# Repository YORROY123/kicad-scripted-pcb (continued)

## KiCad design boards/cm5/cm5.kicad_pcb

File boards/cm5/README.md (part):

# CM5 carrier(進行中)

Raspberry Pi Compute Module 5(含 eMMC)的通用載板,目標是 JLCPCB 能直接 PCBA,CM5 自己插上。

原理圖已完成。PCB 進行中:擺件完成,佈線第一、二階段(兩級降壓的鋪銅與過孔、閘極驅動)完成,第三階段(差分線)全部手佈完成,其餘還沒佈線(交給 freerouting)。3D 預覽在 [`concept/`](concept/README.md)。

## PCB(進行中)

`gen/pcb.py` 讀網表擺出 `cm5.kicad_pcb`;座標與自動擺件在 `gen/placement.py`,3D 預覽也用同一份。
電源級的外層鋪銅、過孔與手佈走線在 `gen/power_stage.py`(見「電源級」「閘極驅動」兩節)。
差分線在 `gen/diff_pairs.py`(見「差分線」)。

- 170 × 120 mm、4 層。固定孔:板子 M3 ×4(H1–H4),CM5 模組 M2.5 ×4(H5–H8)。
- 網路類別(線寬由電流算,見下一節「外層電源走線」):`HV54`(+54V、VIN_RAW;1.4 mm、間距 0.25 mm)、
  `PoE`(POE*;0.5 mm、0.25 mm)、`Switch`(SW、SW3;主路徑是鋪銅)、`Rail5`(+5V;2.7 mm)、`Rail3`(+3V3;1.1 mm)、
  `USB5V`(USB-A / HDMI / USB-C 的 VBUS;0.75 mm)、`Power`(GND 與其他小電源;0.5 mm)。
  54 V 間距取 IPC-2221 表 6-1 的 B4(外層有防焊,51–100 V 0.13 mm)再留餘量;B2(無塗層)的 0.6 mm
  零件本身做不到(RJ45 腳間 0.53、IP804AR 0.25)。
- `cm5.kicad_dru`:同一顆零件的焊盤之間最小 0.1 mm(FSUSB42 MSOP-10 焊盤間只有 0.15 mm),
  走線與過孔仍照網路類別。拿掉這個檔,DRC 會報 FSUSB42 的 8 個間距錯誤。
- 自檢(`lib/pcbgen.py`):焊盤逐腳對網表、courtyard 真實多邊形不重疊、不出板(板邊接頭只查焊盤)。
  `build.ps1` 與 CI 再跑 DRC + 原理圖一致性,除了未連接以外不能有錯誤。
- SW51(FLASH/RUN 滑動開關):撥桿在封裝局部 +y,所以 0°;固定腳到 y=1.83,銅到板邊要 ≥0.5 mm,
  本體退到板邊內 0.75 mm,撥桿伸出約 0.8 mm。外殼開孔時要確認撥得到。

### 差分阻抗(`sim/diff_impedance.py`,結果 `sim/diff_impedance.txt`)

目標照 CM5 規格書 §2.2–2.5:PCIe、USB 3.0、USB 2.0 都是 **90 Ω**,HDMI 與乙太網路 **100 Ω**
(先前這裡寫 PCIe 85 Ω 是錯的)。疊構 JLC04161H-3313(jlcpcb.com/impedance):L1 銅 0.035 mm、
3313 預浸料 0.0994 mm、εr 4.1,差分線走 L1、參考 L2 整片地(L4 對 L3 疊構相同,但 L3 是電源平面,只用來短暫下穿)。`lib/field2d.py` 外推到格距 → 0:

| 用途 | 目標 | 線寬 | 間距 | 算出 |
|---|---|---|---|---|
| PCIe / USB3 / USB2 | 90 Ω | 0.165 mm | 0.15 mm | 90.5 Ω |
| 同上(較緊) | 90 Ω | 0.155 mm | 0.13 mm | 91.0 Ω |
| HDMI / Ethernet | 100 Ω | 0.145 mm | 0.20 mm | 100.2 Ω |
| 同上(較緊) | 100 Ω | 0.130 mm | 0.15 mm | 101.0 Ω |

- 同層鋪銅離差分線 ≥ 0.25 mm 時,阻抗只低 0.4%;0.15 mm 會低 1.5%。
- 防焊漆沒建模(實際再低約 1–3 Ω),所以結果故意落在目標上方。下單前要用 JLC 自己的計算器
  (有建模防焊與梯形線)對一次,並選阻抗控制。
- 換層:L1 ↔ L4 的參考面從 L2(地)換成 L3(電源),旁邊放地過孔接不到 L3,沒有用;要的是 GND–電源的
  縫合電容(見「差分線」待辦)。L4 段不能跨 L3 的 +5V / +3V3 分界。

### 外層電源走線(`gen/pcb.py` 的 `CURRENTS`)

IPC-2221 §6.2 外層公式,外層 1 oz(0.035 mm)、溫升 10 °C。電流取「保護動作前能一直流的電流」:
限流開關用限流**上限**,不是額定。網路類別的線寬比算出的窄,`gen/pcb.py` 就刪掉板檔、回傳失敗。

| 網 | 電流 | 依據 | 需要 | 類別線寬 |
|---|---|---|---|---|
| VIN_RAW、+54V | 3.0 A | 120 W ÷ UVLO 40 V | 1.37 mm | 1.4 mm |
| POE0/1_P、_N | 0.92 A | IP804AR 限流上限(保險絲 1.5 A 只在故障時斷) | 0.27 mm | 0.5 mm |

+5V(→ U62/U63/U70、CM5)與 +3V3(→ M.2)的外層大電流路徑改由「外層供電支線」的鋪銅檢查,
類別線寬降回焊盤放得下的寬度(+5V 0.4、+3V3 0.25),見下一節。
| USBA0/1_VBUS | 1.9 A | AP2171W 限流上限 | 0.73 mm | 0.75 mm |
| HDMI_5V | 1.05 A | TPS2051C 限流上限 | 0.32 mm | 0.75 mm |

- 開關節點與降壓器輸出到內層平面的過孔見下一節「電源級」。
- ⚠ +5V 預算:LM5146 設計 12 A。額定負載 CM5 5 A + 40-pin 1 A + 風扇 0.5 A + USB-A 2 × 1 A + HDMI 0.5 A
  + TPS568230 輸入約 3.0 A(3.3 V × 4 A ÷ 90% ÷ 4.87 V)≈ 12.0 A,剛好到頂。所有限流開關都頂到上限時
  約 14.4 A,會先碰到 LM5146 的限流。要不要降 USB-A 的限流檔或改 12 A 以上的降壓器,佈線前決定。
- `gen/board.py` 的 TPS2051C 註解原本寫限流 0.5–0.9 A,規格書 §6.7(−40–125 °C)是 0.65–1.05 A,已改。

### 外層供電支線(`gen/feeds.py`)與平面扇出(`lib/fanout.py`)

網路類別的線寬整條網共用。+5V 原本 2.7 mm、+3V3 1.1 mm 是照最大的支路算的,結果 LAN7800 / USB2514B
0.25 mm 寬、0.5 mm 腳距的 QFN 腳也要接 1.1 mm 的線,freerouting 扇不出去。現在大電流路徑用固定鋪銅畫死:

| 支線 | 電流 | 做法 | 過孔(每個 0.71 A) |
|---|---|---|---|
| In2 +5V → U62、U63、U70 | 4.85 A | 開關擺在 In2 的 +3V3 區:CM5 模組底邊過孔陣列 → B.Cu 主幹 x 89.5–93.6(避開 USBA0 下穿)→ y 91.3–95.6 橫向 → 每顆 5 腳旁一小塊 F.Cu | 12 / 3 / 3 / 2 |
| In2 +5V → CM5 J1 77–87 | 5 A | 腳下方 F.Cu + 5×2 過孔 | 10 |
| In2 +3V3 → M.2 3V3 腳 | 2.5 A | 右排三組腳外側(卡底下)各一塊 F.Cu | 2 / 3 / 2 |

自檢:載流截面(B.Cu 主幹 3.70 mm ≥ 2.65)、過孔數、F.Cu 小鋪銅的過孔也要落在 B.Cu 主幹上、
每支目標腳最後都接到同網的 In2 平面。突變:U62 過孔 3 → 2、M.2 2/4 腳的鋪銅右移離開焊盤,都會失敗。

平面網路(GND → In1、+3V3 / +5V → In2)的 SMD 焊盤由 `lib/fanout.py` 先打好過孔 + 短線(鎖定):
過孔要落在該網平面的銅上、與異網銅保持兩邊類別較大的間距、孔距 0.25、不進其他零件 courtyard;
短線不比焊盤窄邊寬(CM5 連接器 0.2 mm 焊盤用 0.25 的線離隔壁腳只剩 0.175)。QFN 散熱焊盤
(U40、U41、U50、U61)焊盤內 3×3 過孔。目前 302 個過孔,找不到位置 9 個(C210 / C213 / C230 那裡
In2 是 +3V3 區,沒有 +5V 平面可接,由佈線接到供電支線)。DRC 0。

### 內層電源平面(`gen/pcb.py` 的 `PLANES` / `CORRIDORS`)

- L2(In1.Cu)整片 GND,當 L1 差分線的參考面。
- L3(In2.Cu)分兩塊、中間留 0.5 mm:**+5V** 在右上(x ≥ 60、y ≤ 72),L10 降壓輸出 → CM5、40-pin、風扇;
  **+3V3** 是 L 形(下緣 y ≥ 72 + 左緣 x ≤ 60),L20 降壓輸出 → Hub、LAN7800 ×2 → 往上到 M.2。
- 自檢:每條載流走廊要整塊落在該網的平面裡,而且寬度 ≥ IPC-2221 §6.2 內層公式算出的寬度
  (JLC 內層銅 0.0152 mm、溫升 10 °C;對平面很保守)。不過就刪掉板檔、回傳失敗。

| 網 | 電流 | 走廊寬 | IPC-2221 需要 |
|---|---|---|---|
| +5V(L10 → CM5、40-pin、風扇) | 6.5 A | 71.5 mm | 23.8 mm |
| +3V3(L20 → Hub、LAN7800) | 4.0 A | 47.5 mm | 12.2 mm |
| +3V3(左緣 → M.2) | 2.5 A | 59.5 mm | 6.4 mm |

電流:CM5 5 V 最多 5 A(規格書 §1);M.2 3.3 V 2.5 A(M.2 規範上限);LAN7800 ×2 0.592 A;
40-pin 1 A、風扇 0.5 A、其他 3.3 V 0.3 A 是估計。注意 IPC-2221 這個寬度是 0.5 oz 內層的值:
若整顆降壓器 12 A 都走平面,需要約 55 mm,現在的佈局給得起,但 USB/HDMI 的 5 V 不走平面。
突變:+5V 平面下緣縮到 y = 50 → 走廊落在平面外;+5V 電流改 30 A → 寬度不足,兩者都會失敗。
平面只刪小於 3 mm² 的孤島(`PLANE_MIN_ISLAND_MM2`):40-pin 排針腳之間約 2.2 mm² 的碎銅、過孔陣列之間
< 0.5 mm² 的碎銅都沒接任何東西,以前留著,DRC 報 22 個 isolated_copper 警告;現在 0 個。
還沒接到焊盤的整塊平面不刪。

### 電源級(佈線第一階段;`gen/power_stage.py`)

功率件改成手擺(`gen/placement.py` 的 `PLACE`),照 LM5146 規格書 SNVSBV0A §11.1 與 TPS568230 SLVSEY5C §10.1
(兩份都在 TI 官網);小件仍自動擺,但避開鋪銅與過孔(`power_stage.keepouts()`)。

- **LM5146 → +5V**:Q10 轉 180、Q11 不轉,上下疊。開關節點(Q10 源極、Q11 汲極 → L10)在右側一直線;
  熱迴路(輸入電容 → Q10 汲極 … Q11 源極 → 電容)在左側,C11/C13/C16 的 + 端貼 Q10 汲極、− 端貼 Q11 源極,
  地過孔靠 Q11 源極(§11.1.5)。U10 轉 270,閘極驅動腳朝下正對 Q10;VCC、自舉電容(C20、C21)在 U10 與 Q10 之間。
  54 V 輸入 J20 移到右上,F1 → C10 → 一條 2.1 mm 的 +54V 鋪銅帶往下接輸入電容。
- **TPS568230 → +3V3**:U20 轉 180,VIN 朝右接 C45、SW(19/20 腳)朝下接 L20。整級跨在 In2 分界上:
  輸入取 +5V 平面(5 個過孔),L20 的 2 腳在 +3V3 平面上(8 個過孔)。
- 13 塊 F.Cu 鋪銅都有名字、優先序 1(蓋過之後的整面 GND);80 個過孔鎖定。`lib/route.py` 重新匯入佈線時
  留下它們(`lib/route_test.py`),匯出的 DSN 裡鋪銅是 `plane`、過孔是 `(type fix)`,freerouting 不會動。
- 自檢(`gen/pcb.py` 的 `add_power_stage`,不過就刪掉板檔):每塊鋪銅填得出來、每個過孔在自己網的銅上、
  載流截面整塊有銅、過孔數夠:

| 截面 / 過孔 | 電流 | 寬 | IPC-2221 外層 | 判斷 |
|---|---|---|---|---|
| +54V 帶子(F1 / C10 → 輸入電容) | 3.0 A | 1.7 mm | 1.37 mm | 寬度夠 |
| SW:Q11 汲極 → L10(長 2.35 mm) | 12 A | 4.5 mm | 9.25 mm | 短頸,I²R 37 mW |
| SW3:U20 腳 → L20(長 0.9 mm) | 8 A | 0.85 mm | 5.29 mm | 短頸,I²R 33 mW;受限於 IC 腳寬 |
| +5V:L10 2 腳 → 第一排過孔(長 0.45 mm) | 12 A | 6.3 mm | 9.25 mm | 短頸,I²R 5 mW |
| +3V3:L20 2 腳 → 過孔與輸出電容(長 3.6 mm) | 4.0 A | 2.9 mm | 2.03 mm | 寬度夠 |
| 過孔 L10 → In2 +5V | 12 A | 27 個 | 至少 17 | |
| 過孔 In2 +5V → U20 | 3.0 A | 5 個 | 至少 5 | |
| 過孔 L20 → In2 +3V3 | 4.0 A | 8 個 | 至少 6 | |

  IPC-2221 的寬度是長走線的溫升;開關節點 TI 要求面積越小越好(§11.1.4,它是 EMI 來源),所以 ≤ 3 mm 的
  短頸改算 I²R(銅 1.72e-5 Ω·mm),上限 0.1 W(MOSFET 本身約 1 W 量級)。截面取兩端焊盤之間整段窄處,
  長度照實(只切一薄片的話,任何電流都會被當成短頸放過)。
  突變:拿掉 12 個 +5V 過孔、SW 鋪銅縮窄、過孔移出銅、+3V3 電流改 9 A,四種都會失敗。
- 過孔數改了:以前寫 L10 → +5V 平面 6.5 A、10 個,只算了 CM5、40-pin、風扇;USB-A / HDMI 開關和 U20 的輸入
  也從 +5V 平面取電,LM5146 設計的 12 A 全部要經過這些過孔 → 至少 17 個。
- 還沒做:U10、U20 散熱焊盤下的地過孔(TI §11.1.4):過孔打在焊盤裡要選 JLC 的樹脂塞孔,下單前決定。

### 閘極驅動(佈線第二階段;`gen/power_stage.py` 的 `TRACKS`)

手佈、鎖定的 28 段走線與 4 個過孔(DSN 裡都是 `(type fix)`)。U10 底排腳距 0.5 mm,由左到右
12 GND、13 LO、14 VCC、15 GND、16 NC、17 BST、18 HO、19 SW;腳間出線只能 0.24–0.25 mm,離開腳位才加寬。

- **C21(自舉)不跨 HO**:第一階段以為一定要過孔。改成直放在 16 腳(NC)下:上端直連 17 腳 BST,
  下端一條 0.4 mm 線從 Q10 汲極與閘極焊盤之間直下 SW 鋪銅。HO(18 腳)0.65 mm 直下 Q10 閘極,
  19 腳 SW 在它右側並行回 Q10 源極,即 TI §11.1.2 的「HO 與 SW 成對走」。
- **C20(VCC)轉 180°**:GND 端在 12 腳下、VCC 端在 14 腳下,都是直線;兩焊盤之間 0.65 mm 剛好讓 LO 出去。
- **LO**:過孔換到 B.Cu,0.65 mm 直線到 Q11 閘極,約 12 mm,是唯一換層的閘極線。Q11 的源極要朝左接熱迴路,
  閘極腳就只能在左下角。B.Cu 下面的參考面是 In2 +5V(交流上等同地)。
- **U20 6 腳**(SW3 的另一支,上方是 C47、右邊是 +5V 輸入):C47 往上挪 0.6 mm,6 腳打過孔走 B.Cu 回 SW3 鋪銅。
  B.Cu 走 +5V 腳下方,不經 EP 正下方,留給散熱過孔。
- 也手佈了 C47 → 8 腳 GND 與 +5V 鋪銅、BST3(1 腳 → C49,穿過 SW3 鋪銅的缺口)。VCC3(C48)交給 freerouting。
- 自檢:HO、LO、BST、VCC、SW3、BST3 每條網的焊盤都要接通(`GetConnectedItems`)。
  突變:HO 截短到閘極前、刪掉 6 腳那段,都會失敗。DRC 0 錯誤;未接數(pcbnew 實算)695 → 684。
  `kicad-cli` 報告的「499 unconnected」是它的上限,不是實際數字。

### 差分線(佈線第三階段;`gen/diff_pairs.py`)

每對寫一條中心線,程式切 45° 角、往兩側偏移出 P、N(線寬 / 間距照「差分阻抗」),兩端自動接到 P、N 網的
焊盤;換層處放一對過孔(中心距 1 mm)。走線與過孔都鎖定。對內間距 0.15 mm 比網路類別的 0.2 mm 小,
`cm5.kicad_dru` 每對加一條規則(下限 0.14,留給座標捨入)。

| 對 | 長 | 換層 | 說明 |
|---|---|---|---|
| PCIe REFCLK | 127 mm | 0 | J2 頂排往北 → 向西 → 從 M.2 插座南端繞到腳後 |
| PCIe TX | 128 mm | 0 | 同上 |
| PCIe RX | 122 mm | 1 | 在 x ≈ 45 從 TX 底下穿過(B.Cu 約 4 mm,L3 為 +3V3) |
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
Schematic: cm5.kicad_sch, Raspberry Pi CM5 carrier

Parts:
BT50: CR2032; BatteryHolder_Keystone_3034_1x20mm
C10: 100uF; CP_Radial_D12.5mm_P5.00mm
C11, C12, C13, C14, C15, C16: 4.7uF; C_1210_3225Metric
C17: 100nF; C_0603_1608Metric
C18: 47nF; C_0402_1005Metric
C19: 15pF; C_0402_1005Metric
C20: 2.2uF; C_0603_1608Metric
C21, C47, C49, C51, C60, C70, C71, C72, C73, C74, C75, C76, C77, C88, C101, C102, C103, C104, C106, C107, C108, C109, C111, C112, C113, C114, C115, C120, C121, C131, C132, C133, C134, C136, C137, C138, C139, C141, C142, C143, C144, C145, C150, C151, C200, C202, C203, C204, C205, C206, C207, C212, C215, C222, C230, C231, C240, C241, C242, C243, C244, C245, C246, C247, C248, C249, C250, C251, C252, C253: 100nF; C_0402_1005Metric
C22: 6.8nF; C_0402_1005Metric
C23: 150pF; C_0402_1005Metric
C24: 820pF; C_0402_1005Metric
C30, C31, C32, C33, C34, C40, C41, C42, C43, C45, C46, C50, C220, C221: 47uF; C_1210_3225Metric
C44: 100pF; C_0402_1005Metric
C48, C105, C117, C135, C147, C210, C213: 1uF; C_0402_1005Metric
C82: 1uF; C_1206_3216Metric
C83: 47uF; CP_Elec_10x10
C84, C85, C86, C87, C201: 4.7uF; C_0603_1608Metric
C90, C91: 1nF 2kV; C_1206_3216Metric
C92, C93: 100nF; C_0805_2012Metric
C100, C110, C130, C140: 10uF; C_0805_2012Metric
C118, C119, C148, C149: 27pF; C_0402_1005Metric
C208, C209: 22pF; C_0402_1005Metric
C211, C214: 100uF; CP_Elec_6.3x7.7
D20, D60, D61: SM6T68A; D_SMB
D40, D42, D51: GREEN; LED_0805_2012Metric
D41, D43: YELLOW; LED_0805_2012Metric
D50: RED; LED_0805_2012Metric
D70, D71, D72: USBLC6-2SC6; SOT-23-6
F1: 4A 63V; Fuse_1206_3216Metric
F40, F41: 1.5A; Fuse_1206_3216Metric
J1: CM5 pins 1-100; Amphenol_10164227-1001A1RLF_2x50_P0.4mm
J2: CM5 pins 101-200; Amphenol_10164227-1001A1RLF_2x50_P0.4mm
J20: 54V IN; TerminalBlock_Phoenix_MKDS-1,5-2-5.08_1x02_P5.08mm_Horizont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
J30: HR911130A; RJ45_Hanrun_HR911130A_Horizontal
J40: POE0; RJ45_Amphenol_RJHSE5380
J41: POE1; RJ45_Amphenol_RJHSE5380
J50: USB-C FLASH; USB_C_Receptacle_HRO_TYPE-C-31-M-12
J51: USB-A 1; USB_A_Molex_48037-2200_Horizontal
J52: USB-A 2; USB_A_Molex_48037-2200_Horizontal
J60: M.2 M-key; M.2_Socket_M_TE_1-2199230-6
J70: HDMI; HDMI_A_Molex_208658-1001_Horizontal
J80: GPIO 40-pin; PinHeader_2x20_P2.54mm_Vertical
J81: FAN; JST_SH_SM04B-SRSS-TB_1x04-1MP_P1.00mm_Horizontal
L10: 3.3uH SPM10065VT; L_Bourns_SRP1050WA
L20: 1.5uH IHLP4040; L_Vishay_IHLP-4040
L40, L41: 3.3uH; L_1008_2520Metric
Q10: BSC160N10NS3G; TDSON-8-1
Q11: BSC070N10NS5; TDSON-8-1
R10: 402k; R_0805_2012Metric
R11: 12.4k; R_0402_1005Metric
R12: 33.2k; R_0402_1005Metric
R13: 412; R_0805_2012Metric
R14: 23.2k; R_0402_1005Metric
R15: 4.42k; R_0402_1005Metric
R16: 7.5k; R_0402_1005Metric
R17: 150; R_0402_1005Metric
R18, R74, R75, R76, R77, R78, R102, R132, R205, R206, R207, R208, R209, R230: 10k; R_0402_1005Metric
R21: 91k; R_0402_1005Metric
R22: 20k; R_0402_1005Metric
R23: 330k; R_0402_1005Metric
R24, R200, R201: 5.1k; R_0402_1005Metric
R25, R202, R203, R204: 100k; R_0402_1005Metric
R50, R51: 1k; R_0402_1005Metric
R60, R61, R104, R105, R134, R135: 470; R_0402_1005Metric
R80, R81, R82, R83: 75; R_0603_1608Metric
R100, R130: 2k; R_0402_1005Metric
R101, R131, R210: 12k; R_0402_1005Metric
R211: 1M; R_0402_1005Metric
SW50: POWER; SW_Push_1P1T_NO_CK_KMR2
SW51: FLASH/RUN; SW_SPDT_PCM12
T40, T41: G2423S; Transformer_CNDtek_G2423S
U10: LM5146RGYR; Texas_RGY_R-PVQFN-N20_EP2.05x3.05mm
U20: TPS568230RJER; Texas_RJE0020A_VQFN-20-1EP_3x3mm_P0.45mm_EP0.675x0.76mm
U30, U31: TPD4EUSB30; USON-10_2.5x1.0mm_P0.5mm
U40, U41: LAN7800/Y9X; QFN-48-1EP_7x7mm_P0.5mm_EP5.3x5.3mm
U50: IP804AR; QFN-48-1EP_7x7mm_P0.5mm_EP5.3x5.3mm
U60: FSUSB42MUX; MSOP-10_3x3mm_P0.5mm
U61: USB2514B; QFN-36-1EP_6x6mm_P0.5mm_EP3.7x3.7mm
U62, U63: AP2171W; SOT-23-5
U70: TPS2051CDBV; SOT-23-5
Y40, Y41: 25MHz; Crystal_SMD_3225-4Pin_3.2x2.5mm
Y60: 24MHz; Crystal_SMD_2520-4Pin_2.5x2.0mm

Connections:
+3V3: C40.1, C41.1, C42.1, C43.1, C44.1, C100.1, C101.1, C102.1, C103.1, C104.1, C130.1, C131.1, C132.1, C133.1, C134.1, C201.1, C202.1, C203.1, C204.1, C205.1, C220.1, C221.1, C222.1, C240.1, C246.1, C247.1, C248.1, C249.1, C250.1, C251.1, C252.1, C253.1, D40.2 (A), D41.2 (A), D42.2 (A), D43.2 (A), J60.2 (3.3V), J60.4 (3.3V), J60.12 (3.3V), J60.14 (3.3V), J60.16 (3.3V), J60.18 (3.3V), J60.70 (3.3V), J60.72 (3.3V), J60.74 (3.3V), L20.2, R21.1, R25.1, R205.1, R206.1, R207.1, R208.1, R209.1, U40.14 (VDD_SW_IN), U40.20 (VDDVARIO), U40.23 (VBUS_DET), U40.36 (VDDVARIO), U40.38 (VDD33A), U40.39 (VDDVARIO), U40.46 (VDD33_REG_IN), U41.14 (VDD_SW_IN), U41.20 (VDDVARIO), U41.23 (VBUS_DET), U41.36 (VDDVARIO), U41.38 (VDD33A), U41.39 (VDDVARIO), U41.46 (VDD33_REG_IN), U61.5 (VDDA33), U61.10 (VDDA33), U61.15 (VDD33), U61.23 (VDD33), U61.27 (VBUS_DET), U61.29 (VDDA33), U61.36 (VDDA33)
+5V: C30.1, C31.1, C32.1, C33.1, C34.1, C45.1, C46.1, C47.1, C50.1, C51.1, C210.1, C213.1, C230.1, C241.1, C242.1, C243.1, C244.1, C245.1, J1.77 (5V), J1.79 (5V), J1.81 (5V), J1.83 (5V), J1.85 (5V), J1.87 (5V), J80.2, J80.4, J81.1, L10.2, R14.1, R17.1, U20.2 (VIN), U20.3 (VIN), U20.4 (VIN), U20.5 (VIN), U62.5 (IN), U63.5 (IN), U70.5 (IN)
+54V: C10.1, C11.1, C12.1, C13.1, C14.1, C15.1, C16.1, C17.1, C82.1, C83.1, D20.1 (A1), F1.2, F40.1, F41.1, Q10.5 (D), R10.1, U10.20 (VIN), U50.17 (V54)
BST: C21.1, U10.17 (BST)
BST3: C49.1, U20.1 (BST)
CM5U0_RX_N: C120.2, J2.28 (USB3-0-RX_N)
CM5U0_RX_P: C121.2, J2.30 (USB3-0-RX_P)
CM5U1_RX_N: C151.2, J2.57 (USB3-1-RX_N)
CM5U1_RX_P: C150.2, J2.59 (USB3-1-RX_P)
CM5_1V8: J1.88 (CM5_1.8V), J1.90 (CM5_1.8V)
CM5_3V3: C200.1, D50.2 (A), D51.2 (A), J1.78 (GPIO_VREF), J1.84 (CM5_3.3V), J1.86 (CM5_3.3V), J30.11 (LEDG_A), J30.14 (LEDY_A), J80.1, J80.17, R18.1, R230.1, U60.1 (VCC), U70.4 (EN)
CM5_USB_N: J2.3 (USB_N), U60.4 (D-)
CM5_USB_P: J2.5 (USB_P), U60.3 (D+)
COMP: C23.1, R16.1, U10.4 (COMP)
COMP_RC: C22.1, R16.2
EN_UVLO: R10.2, R11.1, U10.1 (EN/UVLO)
ETH0_N: J1.10 (Ethernet_Pair0_N), J30.3 (MDI0-), U30.4 (D2+), U30.7 (NC)
ETH0_P: J1.12 (Ethernet_Pair0_P), J30.2 (MDI0+), U30.5 (D2-), U30.6 (NC)
ETH1_N: J1.6 (Ethernet_Pair1_N), J30.4 (MDI1+), U30.2 (D1-), U30.9 (NC)
ETH1_P: J1.4 (Ethernet_Pair1_P), J30.7 (MDI1-), U30.1 (D1+), U30.10 (NC)
ETH2_N: J1.9 (Ethernet_Pair2_N), J30.5 (MDI2+), U31.4 (D2+), U31.7 (NC)
ETH2_P: J1.11 (Ethernet_Pair2_P), J30.6 (MDI2-), U31.5 (D2-), U31.6 (NC)
ETH3_N: J1.5 (Ethernet_Pair3_N), J30.9 (MDI3-), U31.2 (D1-), U31.9 (NC)
ETH3_P: J1.3 (Ethernet_Pair3_P), J30.8 (MDI3+), U31.1 (D1+), U31.10 (NC)
ETH_CT: C60.1, J30.1 (CT)
ETH_LEDG_K: J30.12 (LEDG_K), R60.1
ETH_LEDY_K: J30.13 (LEDY_K), R61.1
ETH_nACT: J1.15 (Ethernet_nLED3), R60.2
ETH_nSPD: J1.17 (Ethernet_nLED2), R61.2
FAN_PWM: J1.19 (Fan_PWM), J81.2, R230.2
FAN_TACHO: J1.16 (Fan_Tacho), J81.4
FB: C22.2, C23.2, C24.2, R14.2, R15.1, U10.5 (FB)
FB3: C44.2, R21.2, R22.1, U20.14 (FB)
FB_FF: C24.1, R17.2
GND: BT50.2 (-), C10.2, C11.2, C12.2, C13.2, C14.2, C15.2, C16.2, C17.2, C18.2, C19.2, C20.2, C30.2, C31.2, C32.2, C33.2, C34.2, C40.2, C41.2, C42.2, C43.2, C45.2, C46.2, C47.2, C48.2, C50.2, C51.2, C60.2, C70.2, C71.2, C72.2, C73.2, C74.2, C75.2, C76.2, C77.2, C82.2, C83.2, C84.2, C85.2, C86.2, C87.2, C88.2, C90.2, C91.2, C100.2, C101.2, C102.2, C103.2, C104.2, C105.2, C106.2, C107.2, C108.2, C109.2, C110.2, C111.2, C112.2, C113.2, C114.2, C115.2, C117.2, C118.2, C119.2, C130.2, C131.2, C132.2, C133.2, C134.2, C135.2, C136.2, C137.2, C138.2, C139.2, C140.2, C141.2, C142.2, C143.2, C144.2, C145.2, C147.2, C148.2, C149.2, C200.2, C201.2, C202.2, C203.2, C204.2, C205.2, C206.2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
GPIO2: J1.58 (GPIO2), J80.3
GPIO3: J1.56 (GPIO3), J80.5
GPIO4: J1.54 (GPIO4), J80.7
GPIO5: J1.34 (GPIO5), J80.29
GPIO6: J1.30 (GPIO6), J80.31
GPIO7: J1.37 (GPIO7), J80.26
GPIO8: J1.39 (GPIO8), J80.24
GPIO9: J1.40 (GPIO9), J80.21
GPIO10: J1.44 (GPIO10), J80.19
GPIO11: J1.38 (GPIO11), J80.23
GPIO12: J1.31 (GPIO12), J80.32
GPIO13: J1.28 (GPIO13), J80.33
GPIO14: J1.55 (GPIO14), J80.8
GPIO15: J1.51 (GPIO15), J80.10
GPIO16: J1.29 (GPIO16), J80.36
GPIO17: J1.50 (GPIO17), J80.11
GPIO18: J1.49 (GPIO18), J80.12
GPIO19: J1.26 (GPIO19), J80.35
GPIO20: J1.27 (GPIO20), J80.38
GPIO21: J1.25 (GPIO21), J80.40
GPIO22: J1.46 (GPIO22), J80.15
GPIO23: J1.47 (GPIO23), J80.16
GPIO24: J1.45 (GPIO24), J80.18
GPIO25: J1.41 (GPIO25), J80.22
GPIO26: J1.24 (GPIO26), J80.37
GPIO27: J1.48 (GPIO27), J80.13
HDMI0_CEC: J2.51 (HDMI0_CEC), J70.13 (CEC)
HDMI0_CK_N: J2.90 (HDMI0_CLK_N), J70.12 (CK-)
HDMI0_CK_P: J2.88 (HDMI0_CLK_P), J70.10 (CK+)
HDMI0_D0_N: J2.84 (HDMI0_TX0_N), J70.9 (D0-)
HDMI0_D0_P: J2.82 (HDMI0_TX0_P), J70.7 (D0+)
HDMI0_D1_N: J2.78 (HDMI0_TX1_N), J70.6 (D1-)
HDMI0_D1_P: J2.76 (HDMI0_TX1_P), J70.4 (D1+)
HDMI0_D2_N: J2.72 (HDMI0_TX2_N), J70.3 (D2-)
HDMI0_D2_P: J2.70 (HDMI0_TX2_P), J70.1 (D2+)
HDMI0_HPD: J2.53 (HDMI0_HOTPLUG), J70.19 (HPD)
HDMI0_SCL: J2.100 (HDMI0_SCL), J70.15 (SCL)
HDMI0_SDA: J2.99 (HDMI0_SDA), J70.16 (SDA)
HDMI_5V: C231.1, J70.18 (+5V), U70.1 (OUT)
HO: Q10.4 (G), U10.18 (HO)
HUB_CFG0: R202.1, U61.24 (SCL/SMBCLK/CFG_SEL0)
HUB_CFG1: R203.1, U61.25 (HS_IND/CFG_SEL1)
HUB_CRFILT: C206.1, U61.14 (CRFILT)
HUB_DIS3: R205.2, U61.6 (USBDM_DN3/PRT_DIS_M3), U61.7 (USBDP_DN3/PRT_DIS_P3)
HUB_DIS4: R206.2, U61.8 (USBDM_DN4/PRT_DIS_M4), U61.9 (USBDP_DN4/PRT_DIS_P4)
HUB_NONREM1: R204.1, U61.22 (SDA/SMBDATA/NON_REM1)
HUB_OCN34: R207.2, U61.19 (OCS_N3), U61.21 (OCS_N4)
HUB_PLLFILT: C207.1, U61.34 (PLLFILT)
HUB_RBIAS: R210.1, U61.35 (RBIAS)
HUB_UP_DN: U60.8 (HSD2-), U61.30 (USBDM_UP)
HUB_UP_DP: U60.9 (HSD2+), U61.31 (USBDP_UP)
HUB_XI: C208.1, R211.1, U61.33 (XTALIN/CLKIN), Y60.1
HUB_XO: C209.1, R211.2, U61.32 (XTALOUT), Y60.3
ID_SC: J1.35 (ID_SC), J80.28
ID_SD: J1.36 (ID_SD), J80.27
ILIM: C19.1, R13.1, U10.11 (ILIM)
IP_1V8: C87.1, U50.21 (V1P8)
IP_3V3: C85.1, C86.1, R74.1, R75.1, R76.1, U50.20 (V3P3), U50.44 (DV3P3)
IP_5V: C84.1, U50.19 (V5), U50.22 (VPP)
IP_LEDCLK: R77.1, U50.37 (LED_CLK)
IP_LEDDAT: R78.1, U50.38 (LED_DAT)
IP_RSTN: C88.1, R74.2, U50.45 (RstN)
IP_SCL: R75.2, U50.39 (SCL/EE_CLK)
IP_SDA: R76.2, U50.41 (SDAI/EE_DAT)
LAN0_1V2: C110.1, C111.1, C112.1, C113.1, C114.1, C115.1, L40.2, U40.15 (VDD12_SW_FB), U40.21 (VDD12CORE), U40.25 (VDD12A), U40.30 (VDD12A), U40.42 (VDD12CORE), U40.44 (VDD12A)
LAN0_2V5: C105.1, C106.1, C107.1, C108.1, C109.1, U40.3 (VDD25A), U40.6 (VDD25A), U40.9 (VDD25A), U40.12 (VDD25A), U40.45 (VDD25_REG_OUT)
LAN0_DM: J2.36 (USB3-0-DM), U40.27 (USB2_DM)
LAN0_DP: J2.34 (USB3-0-DP), U40.26 (USB2_DP)
LAN0_EEDI: R102.1, U40.17 (EEDI/GPIO1)
LAN0_FILT: C117.1, U40.48 (REF_FILT)
LAN0_LEDG_K: R104.2, U40.18 (EEDO/LED0/GPIO2)
LAN0_LEDG_K2: D40.1 (K), R104.1
LAN0_LEDY_K: R105.2, U40.19 (EECLK/LED1/GPIO3)
LAN0_LEDY_K2: D41.1 (K), R105.1
LAN0_RBIAS: R101.1, U40.37 (USBRBIAS)
LAN0_REXT: R100.1, U40.47 (REF_REXT)
LAN0_RX_N: J2.40 (USB3-0-TX_N), U40.31 (USB3_RXDP)
LAN0_RX_P: J2.42 (USB3-0-TX_P), U40.32 (USB3_RXDM)
LAN0_SW: L40.1, U40.13 (VDD12_SW_OUT)
LAN0_TR0N: T40.22 (TD1-), U40.2 (TR0N)
LAN0_TR0P: T40.23 (TD1+), U40.1 (TR0P)
LAN0_TR1N: T40.19 (TD2-), U40.5 (TR1N)
LAN0_TR1P: T40.20 (TD2+), U40.4 (TR1P)
LAN0_TR2N: T40.16 (TD3-), U40.8 (TR2N)
LAN0_TR2P: T40.17 (TD3+), U40.7 (TR2P)
LAN0_TR3N: T40.13 (TD4-), U40.11 (TR3N)
LAN0_TR3P: T40.14 (TD4+), U40.10 (TR3P)
LAN0_TX_N: C121.1, U40.29 (USB3_TXDM)
LAN0_TX_P: C120.1, U40.28 (USB3_TXDP)
LAN0_XI: C118.1, U40.40 (XI), Y40.1
LAN0_XO: C119.1, U40.41 (XO), Y40.3
LAN1_1V2: C140.1, C141.1, C142.1, C143.1, C144.1, C145.1, L41.2, U41.15 (VDD12_SW_FB), U41.21 (VDD12CORE), U41.25 (VDD12A), U41.30 (VDD12A), U41.42 (VDD12CORE), U41.44 (VDD12A)
LAN1_2V5: C135.1, C136.1, C137.1, C138.1, C139.1, U41.3 (VDD25A), U41.6 (VDD25A), U41.9 (VDD25A), U41.12 (VDD25A), U41.45 (VDD25_REG_OUT)
LAN1_DM: J2.65 (USB3-1-DM), U41.27 (USB2_DM)
LAN1_DP: J2.63 (USB3-1-DP), U41.26 (USB2_DP)
LAN1_EEDI: R132.1, U41.17 (EEDI/GPIO1)
LAN1_FILT: C147.1, U41.48 (REF_FILT)
LAN1_LEDG_K: R134.2, U41.18 (EEDO/LED0/GPIO2)
LAN1_LEDG_K2: D42.1 (K), R134.1
LAN1_LEDY_K: R135.2, U41.19 (EECLK/LED1/GPIO3)
LAN1_LEDY_K2: D43.1 (K), R135.1
LAN1_RBIAS: R131.1, U41.37 (USBRBIAS)
LAN1_REXT: R130.1, U41.47 (REF_REXT)
LAN1_RX_N: J2.69 (USB3-1-TX_N), U41.32 (USB3_RXDM)
LAN1_RX_P: J2.71 (USB3-1-TX_P), U41.31 (USB3_RXDP)
LAN1_SW: L41.1, U41.13 (VDD12_SW_OUT)
LAN1_TR0N: T41.22 (TD1-), U41.2 (TR0N)
LAN1_TR0P: T41.23 (TD1+), U41.1 (TR0P)
LAN1_TR1N: T41.19 (TD2-), U41.5 (TR1N)
LAN1_TR1P: T41.20 (TD2+), U41.4 (TR1P)
LAN1_TR2N: T41.16 (TD3-), U41.8 (TR2N)
LAN1_TR2P: T41.17 (TD3+), U41.7 (TR2P)
LAN1_TR3N: T41.13 (TD4-), U41.11 (TR3N)
LAN1_TR3P: T41.14 (TD4+), U41.10 (TR3P)
LAN1_TX_N: C151.1, U41.29 (USB3_TXDM)
LAN1_TX_P: C150.1, U41.28 (USB3_TXDP)
LAN1_XI: C148.1, U41.40 (XI), Y41.1
LAN1_XO: C149.1, U41.41 (XO), Y41.3
LED_ACT_K: D51.1 (K), R51.1
LED_PWR_K: D50.1 (K), R50.1
LED_nACT: J1.21 (LED_nACT), R51.2
LED_nPWR: J1.95 (LED_nPWR), R50.2
LO: Q11.4 (G), U10.13 (LO)
MODE3: R23.2, R24.1, U20.15 (MODE)
PCIE_CLK_N: J2.12 (PCIe_CLK_N), J60.53 (REFCLKn)
PCIE_CLK_P: J2.10 (PCIe_CLK_P), J60.55 (REFCLKp)
PCIE_RX_N: J2.18 (PCIe_RX_N), J60.41 (PERn0/SATA-B+)
PCIE_RX_P: J2.16 (PCIe_RX_P), J60.43 (PERp0/SATA-B-)
PCIE_TX_N: J2.24 (PCIe_TX_N), J60.47 (PETn0/SATA-A-)
PCIE_TX_P: J2.22 (PCIe_TX_P), J60.49 (PETp0/SATA-A+)
PCIE_nCLKREQ: J2.2 (PCIe_CLK_nREQ), J60.52 (~CLKREQ)
PCIE_nRST: J2.9 (PCIe_nRST), J60.50 (~PERST)
PCIE_nWAKE: J2.4 (PCIE_nWAKE), J60.54 (~PEWAKE)
PG_3V3: R25.2, U20.9 (PGOOD), U40.35 (RESET_N/PME_CLEAR), U41.35 (RESET_N/PME_CLEAR), U61.26 (RESET_N)
PG_5V: R18.2, U10.10 (PGOOD), U20.12 (EN)
POE0_A_N: J40.2, T40.3 (MX1-)
POE0_A_P: J40.1, T40.2 (MX1+)
POE0_BOB: C90.1, R80.2, R81.2
POE0_B_N: J40.6, T40.6 (MX2-)
POE0_B_P: J40.3, T40.5 (MX2+)
POE0_CT3: R80.1, T40.7 (MCT3)
POE0_CT4: R81.1, T40.10 (MCT4)
POE0_C_N: J40.5, T40.9 (MX3-)
POE0_C_P: J40.4, T40.8 (MX3+)
POE0_D_N: J40.8, T40.12 (MX4-)
POE0_D_P: J40.7, T40.11 (MX4+)
POE0_N: C92.2, D60.2 (A2), T40.1 (MCT1), U50.3 (PortN0)
POE0_P: C92.1, D60.1 (A1), F40.2, T40.4 (MCT2)
POE0_TCT1: C70.1, T40.24 (TCT1)
POE0_TCT2: C71.1, T40.21 (TCT2)
POE0_TCT3: C72.1, T40.18 (TCT3)
POE0_TCT4: C73.1, T40.15 (TCT4)
POE1_A_N: J41.2, T41.3 (MX1-)
POE1_A_P: J41.1, T41.2 (MX1+)
POE1_BOB: C91.1, R82.2, R83.2
POE1_B_N: J41.6, T41.6 (MX2-)
POE1_B_P: J41.3, T41.5 (MX2+)
POE1_CT3: R82.1, T41.7 (MCT3)
POE1_CT4: R83.1, T41.10 (MCT4)
POE1_C_N: J41.5, T41.9 (MX3-)
POE1_C_P: J41.4, T41.8 (MX3+)
POE1_D_N: J41.8, T41.12 (MX4-)
POE1_D_P: J41.7, T41.11 (MX4+)
POE1_N: C93.2, D61.2 (A2), T41.1 (MCT1), U50.5 (PortN1)
POE1_P: C93.1, D61.1 (A1), F41.2, T41.4 (MCT2)
POE1_TCT1: C74.1, T41.24 (TCT1)
POE1_TCT2: C75.1, T41.21 (TCT2)
POE1_TCT3: C76.1, T41.18 (TCT3)
POE1_TCT4: C77.1, T41.15 (TCT4)
PWR_BUT: J1.92 (PWR_Button), SW50.1
RT: R12.1, U10.2 (RT)
SS: C18.1, U10.3 (SS/TRK)
SW: C21.2, L10.1, Q10.1 (S), Q10.2 (S), Q10.3 (S), Q11.5 (D), R13.2, U10.19 (SW)
SW3: C49.2, L20.1, U20.6 (SW), U20.19 (SW), U20.20 (SW)
USBA0_DN: D71.3 (I/O2), D71.4 (I/O2), J51.2 (D-), U61.1 (USBDM_DN1/PRT_DIS_M1)
USBA0_DP: D71.1 (I/O1), D71.6 (I/O1), J51.3 (D+), U61.2 (USBDP_DN1/PRT_DIS_P1)
USBA0_EN: U61.12 (PRTPWR1/BC_EN1), U62.4 (EN)
USBA0_OCN: R208.2, U61.13 (OCS_N1), U62.3 (~FLG)
USBA0_VBUS: C211.1, C212.1, D71.5 (VBUS), J51.1 (VBUS), U62.1 (OUT)
USBA1_DN: D72.3 (I/O2), D72.4 (I/O2), J52.2 (D-), U61.3 (USBDM_DN2/PRT_DIS_M2)
USBA1_DP: D72.1 (I/O1), D72.6 (I/O1), J52.3 (D+), U61.4 (USBDP_DN2/PRT_DIS_P2)
USBA1_EN: U61.16 (PRTPWR2/BC_EN2), U63.4 (EN)
USBA1_OCN: R209.2, U61.17 (OCS_N2), U63.3 (~FLG)
USBA1_VBUS: C214.1, C215.1, D72.5 (VBUS), J52.1 (VBUS), U63.1 (OUT)
USBC_CC1: J50.A5 (CC1), R200.1
USBC_CC2: J50.B5 (CC2), R201.1
USBC_DN: D70.3 (I/O2), D70.4 (I/O2), J50.A7 (D-), J50.B7 (D-), U60.6 (HSD1-)
USBC_DP: D70.1 (I/O1), D70.6 (I/O1), J50.A6 (D+), J50.B6 (D+), U60.7 (HSD1+)
USBC_VBUS: D70.5 (VBUS), J50.A4 (VBUS), J50.A9 (VBUS), J50.B4 (VBUS), J50.B9 (VBUS)
USB_OTG_ID: J2.1 (USB_OTG_ID), SW51.3 (C)
VBAT: BT50.1 (+), J1.76 (VBAT)
VCC: C20.1, U10.14 (VCC)
VCC3: C48.1, R23.1, U20.17 (VCC)
VIN_RAW: F1.1, J20.1
nRPIBOOT: J1.93 (nRPIBOOT), SW51.1 (A), U60.2 (SEL)

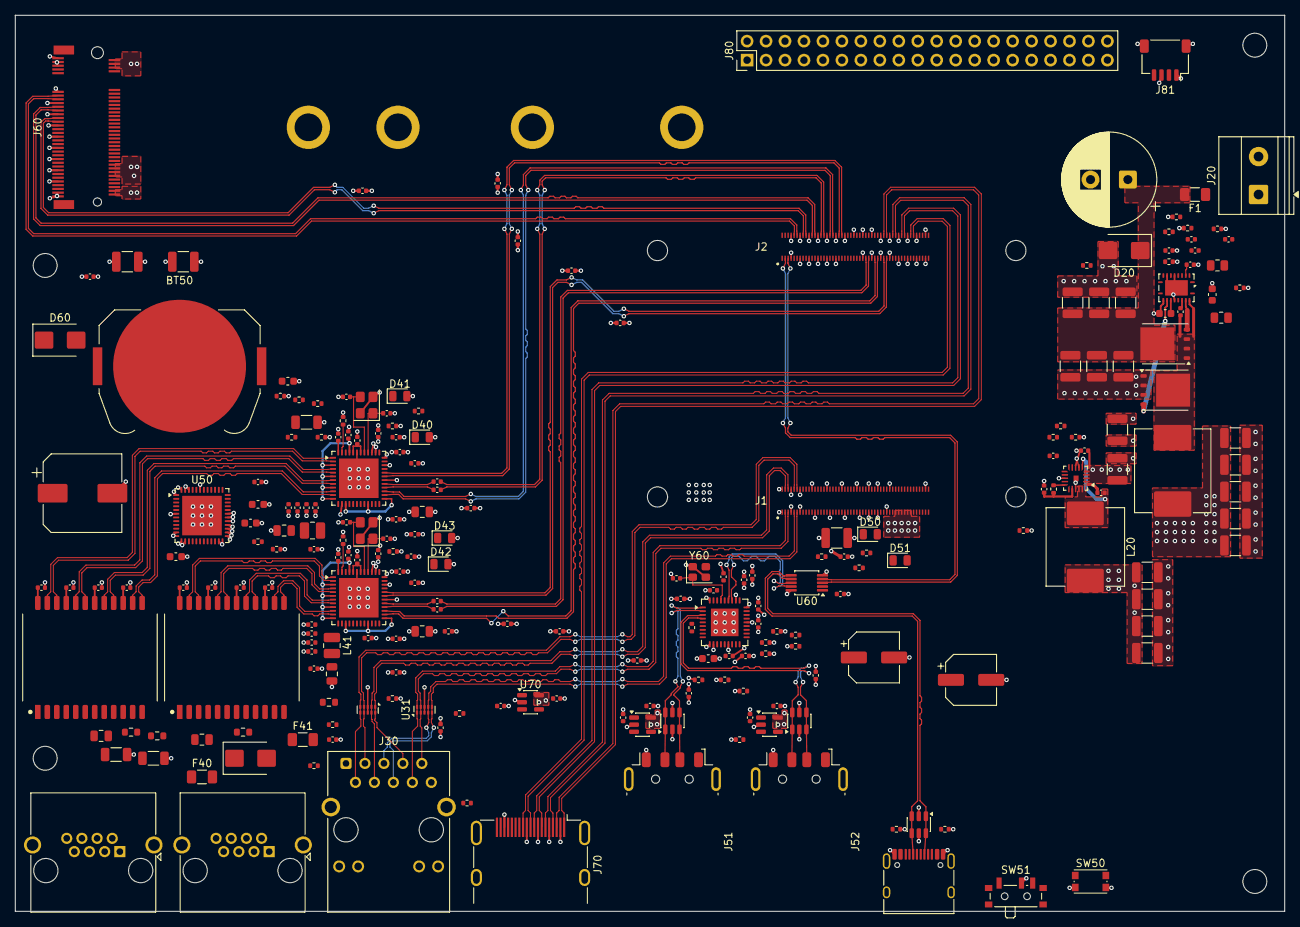
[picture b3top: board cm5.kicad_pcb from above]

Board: 4 copper layers, 170.0 x 120.0 mm, 241 parts (0 on the bottom side), 230 nets.

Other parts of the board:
H1, H2, H3, H4: MountingHole_3.2mm_M3
H5, H6, H7, H8: MountingHole_2.7mm_M2.5

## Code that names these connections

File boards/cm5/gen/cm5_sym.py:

"""Raspberry Pi Compute Module 5 的符號:兩顆 100 腳 DF40 各一個符號(CM5_J1、CM5_J2)。

KiCad 10 的 MCU_Module 只到 CM3,CM4/CM5 都沒有,所以自己畫。

腳位表照抄《Raspberry Pi Compute Module 5 datasheet》4.2 Pinout(cm5-datasheet.pdf)。
`--verify <datasheet 文字檔>` 會從 pdftotext -layout 的輸出重新解析一次,逐腳比對;
規格書不放進 repo(版權),所以預設不跑,改腳位表時一定要跑。

焊盤編號:CM5 的 1–100 腳在第一顆連接器、101–200 在第二顆。符號腳號就是焊盤號
(1–100),CM5_J2 的焊盤 n = CM5 第 100+n 腳。腳名保留規格書原名,J2 另外在名稱後面
不加註 —— 要看 CM5 腳號就 +100。
封裝 CM5:Amphenol_10164227-1001A1RLF_2x50_P0.4mm 由 cm5_fp.py 生成:焊盤 n = CM5 腳 n
(J2 為 100+n),已用 --compare 對官方 CM5 IO Board 封裝逐焊盤確認(200/200)。

用法: python cm5_sym.py [--verify cm5.txt]  → 寫 ../symbols/CM5.kicad_sym
"""
from __future__ import annotations

import re
import sys
from pathlib import Path

HERE = Path(__file__).resolve().parent
OUT = HERE.parent / "symbols" / "CM5.kicad_sym"

# CM5 腳 1..200 的名稱,照規格書順序,每列 10 腳
PINOUT = """
GND GND Ethernet_Pair3_P Ethernet_Pair1_P Ethernet_Pair3_N Ethernet_Pair1_N GND GND Ethernet_Pair2_N Ethernet_Pair0_N
Ethernet_Pair2_P Ethernet_Pair0_P GND GND Ethernet_nLED3 Fan_Tacho Ethernet_nLED2 Ethernet_SYNC_OUT Fan_PWM EEPROM_nWP
LED_nACT GND GND GPIO26 GPIO21 GPIO19 GPIO20 GPIO13 GPIO16 GPIO6
GPIO12 GND GND GPIO5 ID_SC ID_SD GPIO7 GPIO11 GPIO8 GPIO9
GPIO25 GND GND GPIO10 GPIO24 GPIO22 GPIO23 GPIO27 GPIO18 GPIO17
GPIO15 GND GND GPIO4 GPIO14 GPIO3 SD_CLK GPIO2 GND GND
SD_DAT3 SD_CMD SD_DAT0 SD_DAT5 GND GND SD_DAT1 SD_DAT4 SD_DAT2 SD_DAT7
GND SD_DAT6 SD_VDD_OVERRIDE GND SD_PWR_ON VBAT 5V GPIO_VREF 5V SCL0
5V SDA0 5V CM5_3.3V 5V CM5_3.3V 5V CM5_1.8V WL_nDisable CM5_1.8V
BT_nDisable PWR_Button nRPIBOOT CC1 LED_nPWR CC2 CAM_GPIO0 GND PMIC_Enable CAM_GPIO1
USB_OTG_ID PCIe_CLK_nREQ USB_N PCIE_nWAKE USB_P PCIE_PWR_EN GND GND PCIe_nRST PCIe_CLK_P
VBUS_EN PCIe_CLK_N GND GND MIPI0_D0_N PCIe_RX_P MIPI0_D0_P PCIe_RX_N GND GND
MIPI0_D1_N PCIe_TX_P MIPI0_D1_P PCIe_TX_N GND GND MIPI0_C_N USB3-0-RX_N MIPI0_C_P USB3-0-RX_P
GND GND MIPI0_D2_N USB3-0-DP MIPI0_D2_P USB3-0-DM GND GND MIPI0_D3_N USB3-0-TX_N
MIPI0_D3_P USB3-0-TX_P HDMI1_HOTPLUG GND HDMI1_SDA HDMI1_TX2_P HDMI1_SCL HDMI1_TX2_N HDMI1_CEC GND
HDMI0_CEC HDMI1_TX1_P HDMI0_HOTPLUG HDMI1_TX1_N GND GND USB3-1-RX_N HDMI1_TX0_P USB3-1-RX_P HDMI1_TX0_N
GND GND USB3-1-DP HDMI1_CLK_P USB3-1-DM HDMI1_CLK_N GND GND USB3-1-TX_N HDMI0_TX2_P
USB3-1-TX_P HDMI0_TX2_N GND GND MIPI1_D0_N HDMI0_TX1_P MIPI1_D0_P HDMI0_TX1_N GND GND
MIPI1_D1_N HDMI0_TX0_P MIPI1_D1_P HDMI0_TX0_N GND GND MIPI1_C_N HDMI0_CLK_P MIPI1_C_P HDMI0_CLK_N
GND GND MIPI1_D2_N MIPI1_D3_N MIPI1_D2_P MIPI1_D3_P GND GND HDMI0_SDA HDMI0_SCL
""".split()
assert len(PINOUT) == 200, len(PINOUT)
NAME = {i + 1: n for i, n in enumerate(PINOUT)}


def etype(name: str, pin: int = 0) -> str:
    """ERC 用的電氣類型。電源腳照方向給,其餘一律 passive(避免 input 沒驅動的假警告)。"""
    if name in ("GND", "5V", "GPIO_VREF", "VBAT"):
        return "power_in"
    if name in ("CM5_3.3V", "CM5_1.8V"):
        # 每路兩支腳(84/86、88/90)是同一個輸出;兩支都標 power_out,ERC 會當成兩個電源互接
        return "power_out" if pin in (84, 88) else "passive"
    if name in ("LED_nPWR", "LED_nACT", "Ethernet_nLED2", "Ethernet_nLED3"):   # 模組內是開汲極拉低(VOL < 0.4V),review.py 的 led-current 要知道
        return "open_collector"
    return "passive"


def verify(txt: Path) -> int:
    """從規格書文字檔(pdftotext -layout -enc UTF-8)的 4.2 Pinout 重新解析,逐腳比對。"""
    lines = txt.read_text(encoding="utf-8").splitlines()
    start = next(i for i, s in enumerate(lines) if re.match(r"^\s*4\.2\. Pinout\s*$", s))
    got: dict[int, str] = {}
    for s in lines[start:start + 600]:
        m = re.match(r"^\s*(\d{1,3})\s+(\S+)\s", s + " ")
        if m and 1 <= int(m.group(1)) <= 200 and int(m.group(1)) not in got:
            got[int(m.group(1))] = m.group(2)
    bad = [n for n in range(1, 201) if got.get(n) != NAME[n]]
    for n in bad:
        print(f"  腳 {n}: 表={NAME[n]} 規格書={got.get(n)}")
    print(f"verify: {200 - len(bad)}/200 一致")
    return 1 if bad else 0


def font() -> str:
    return "(effects\n\t\t\t\t\t\t(font\n\t\t\t\t\t\t\t(size 1.27 1.27)\n\t\t\t\t\t\t)\n\t\t\t\t\t)"


def prop(key: str, val: str, x: float, y: float, hide: bool) -> str:
    h = "\n\t\t\t(hide yes)" if hide else ""
    return (f'\t\t(property "{key}" "{val}"\n\t\t\t(at {x} {y} 0)\n\t\t\t(show_name no)\n'
            f'\t\t\t(do_not_autoplace no){h}\n\t\t\t(effects\n\t\t\t\t(font\n\t\t\t\t\t(size 1.27 1.27)\n'
            f'\t\t\t\t)\n\t\t\t\t(justify left)\n\t\t\t)\n\t\t)\n')


P = 2.54
HALF_W = 25.4          # 本體半寬:兩側腳名最長 17 字,約 17 mm,中間留空
ROWS = 50


def symbol(sym: str, first: int, desc: str) -> str:
    top = (ROWS - 1) / 2 * P            # 第一列 y
    body_h = top + P
    out = [f'\t(symbol "{sym}"\n\t\t(pin_names\n\t\t\t(offset 0.762)\n\t\t)\n'
           "\t\t(exclude_from_sim no)\n\t\t(in_bom yes)\n\t\t(on_board yes)\n\t\t(in_pos_files yes)\n"
           "\t\t(duplicate_pin_numbers_are_jumpers no)\n"]
    out.append(prop("Reference", "J", -HALF_W, round(body_h + P, 2), False))
    out.append(prop("Value", sym, 0, round(body_h + P, 2), False))
    out.append(prop("Footprint", "CM5:Amphenol_10164227-1001A1RLF_2x50_P0.4mm", 0, 0, True))
    out.append(prop("Datasheet", "https://datasheets.raspberrypi.com/cm5/cm5-datasheet.pdf", 0, 0, True))
    out.append(prop("Description", desc, 0, 0, True))
    out.append(f'\t\t(symbol "{sym}_0_1"\n\t\t\t(rectangle\n\t\t\t\t(start {-HALF_W} {body_h})\n'
               f"\t\t\t\t(end {HALF_W} {-body_h})\n\t\t\t\t(stroke\n\t\t\t\t\t(width 0.254)\n"
               "\t\t\t\t\t(type default)\n\t\t\t\t)\n\t\t\t\t(fill\n\t\t\t\t\t(type background)\n"
               "\t\t\t\t)\n\t\t\t)\n\t\t)\n")
    out.append(f'\t\t(symbol "{sym}_1_1"\n')
    for pad in range(1, 101):
        name = NAME[first + pad - 1]
        row = (pad - 1) // 2
        y = round(top - row * P, 2)
        x, ang = (-(HALF_W + P), 0) if pad % 2 else (HALF_W + P, 180)
        out.append(f"\t\t\t(pin {etype(name, first + pad - 1)} line\n\t\t\t\t(at {x} {y} {ang})\n\t\t\t\t(length {P})\n"
                   f'\t\t\t\t(name "{name}"\n\t\t\t\t\t{font()}\n\t\t\t\t)\n'
                   f'\t\t\t\t(number "{pad}"\n\t\t\t\t\t{font()}\n\t\t\t\t)\n\t\t\t)\n')
    out.append("\t\t)\n\t\t(embedded_fonts no)\n\t)\n")
    return "".join(out)


def main() -> int:
    if "--verify" in sys.argv:
        rc = verify(Path(sys.argv[sys.argv.index("--verify") + 1]))
        if rc:
            return rc
    text = ("(kicad_symbol_lib\n\t(version 20251024)\n\t(generator \"kicad-scripted-pcb\")\n"
            + symbol("CM5_J1", 1, "Raspberry Pi CM5, connector 1 (CM5 pins 1-100)")
            + symbol("CM5_J2", 101, "Raspberry Pi CM5, connector 2 (pad n = CM5 pin 100+n)")
            + ")\n")
    OUT.parent.mkdir(parents=True, exist_ok=True)
    OUT.write_text(text, encoding="utf-8", newline="\n")
    print(f"wrote {OUT}")
    return 0


if __name__ == "__main__":
    sys.exit(main())

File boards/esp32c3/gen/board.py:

"""ESP32-C3 最小系统板:USB-C 供电 + 原生 USB 下载/调试 + 3.3V LDO + 按键 + LED + 排针。

依据 Espressif《ESP32-C3 硬件设计指南》与 ESP32-C3-WROOM-02 规格书:
  - USB D-/D+ 直连 GPIO18/GPIO19(芯片内置 USB Serial/JTAG,不需要 USB 转串口芯片)
  - EN:10k 上拉 + 1µF 对地(上电复位延时),RESET 键把 EN 拉低
  - GPIO9 是启动模式脚:上拉 = 从 flash 启动;按住 BOOT 键(拉低)上电 = 下载模式
  - GPIO2、GPIO8 是 strapping 脚,上电时须为高,各 10k 上拉
  - 用户 LED 接 GPIO10(不是 strapping 脚,接 LED 不影响启动)

电源吸取 usbc-ldo 那块板子的模拟教训(见 AGENTS.md):
  - 不串二极管、LDO 用 LP38693MP-3.3(壓差 ~330mV @0.5A;輸入耐壓 12V,扛得住熱插拔過衝)
  - 插入浪湧:模組內部還有約 12.3µF,直接接 VBUS 會灌進約 79µC(> USB 2.0 的 50µC)
    → 加 P-MOSFET 軟啟動(Q1,見下方與 sim/softstart_sim.py)

画法:网络标签式。每个引脚沿「离开器件」的方向拉 2.54mm 短线挂一个全局标签,
电路本身就是下面那张「引脚 → 网络」对照表,审查时逐行对 datasheet 即可。
"""
import json
import math
import sys
from pathlib import Path

HERE = Path(__file__).resolve().parent
SHARED = HERE.parents[2] / "lib"
sys.path.insert(0, str(SHARED))
from schgen import Part, Schematic  # noqa: E402

G = 1.27
STUB = 2 * G


def g(n: float) -> float:
    return round(n * G, 4)


s = Schematic(title="ESP32-C3 minimal board (USB-C, native USB)")


def outward(part: Part, pin: str) -> tuple[float, float]:
    """引脚「离开器件」的单位方向(图纸坐标,y 向下)。

    符号库里引脚的 angle 指向器件本体;反过来就是向外。还要套上器件的旋转。
    """
    part.pin_xy(pin)                       # 确保 _pins 已载入
    a = math.radians(part._pins[pin]["angle"] + 180)
    vx, vy = math.cos(a), -math.sin(a)     # 符号库 y 向上 → 图纸 y 向下
    r = math.radians(part.rotation)
    rx = vx * math.cos(r) - vy * math.sin(r)
    ry = vx * math.sin(r) + vy * math.cos(r)
    return round(rx), round(ry)


# 标签朝向:文字顺着短线方向往外长,不压在器件上
LABEL_ROT = {(1, 0): 0, (-1, 0): 180, (0, -1): 90, (0, 1): 270}

# 设计意图:每个引脚应接到哪个网(None = 刻意不接)。写成 JSON 交给 check_netlist.py
# 和 kicad-cli 导出的网表逐脚比对 —— ERC 默认不报「全局标签只出现一次」,
# 标签名打错字会变成一个孤立的网,只有比对网表才抓得到。
EXPECTED: dict = {}


def attach(part: Part, pins: dict) -> Part:
    """按「引脚 → 网络」接线;网络为 None 表示刻意不接(打 NC 记号)。

    同一坐标上的堆叠引脚(USB-C 的 A4/A9/B4/B9 等)只挂一次标签。
    """
    seen = set()
    for pin, net in pins.items():
        if not part.ref.startswith("#"):
            EXPECTED[f"{part.ref}.{pin}"] = net
        xy = part.pin_xy(pin)
        if xy in seen:
            continue
        seen.add(xy)
        if net is None:
            s.no_connect(part, pin)
            continue
        ox, oy = outward(part, pin)
        s.label(net, part, pin, dx=ox * STUB, dy=oy * STUB, rotation=LABEL_ROT[(ox, oy)])
    return part


def add(ref, lib, name, x, y, value, footprint, pins, rot=0.0):
    p = s.add(Part(ref, lib, name, g(x), g(y), value=value, footprint=footprint, rotation=rot))
    return attach(p, pins)


def flag(net: str, x: float, y: float) -> None:
    """PWR_FLAG:告诉 ERC 这个网确实由外部供电(USB 进来的 VBUS、以及 GND)。"""
    p = s.add(Part(f"#FLG{len(s.parts):02d}", "power", "PWR_FLAG", g(x), g(y),
                   value="PWR_FLAG", fields_hidden=True))
    attach(p, {"1": net})


R0402 = "Resistor_SMD:R_0402_1005Metric"
C0402 = "Capacitor_SMD:C_0402_1005Metric"
C0805 = "Capacitor_SMD:C_0805_2012Metric"
LED0805 = "LED_SMD:LED_0805_2012Metric"
BUTTON = "Button_Switch_SMD:SW_Push_1P1T_NO_CK_KMR2"

# ── USB-C 输入 ──────────────────────────────────────────────────────────
add("J1", "Connector", "USB_C_Receptacle_USB2.0_16P", 30, 60, "USB-C",
    "Connector_USB:USB_C_Receptacle_HRO_TYPE-C-31-M-12", {
        "A4": "VBUS", "A9": "VBUS", "B4": "VBUS", "B9": "VBUS",
        "A1": "GND", "A12": "GND", "B1": "GND", "B12": "GND", "SH": "GND",
        "A5": "CC1", "B5": "CC2",
        # USB-C 正反插:A、B 两面的 D+/D- 在这里并到同一个网
        "A6": "USB_DP", "B6": "USB_DP", "A7": "USB_DN", "B7": "USB_DN",
        "A8": None, "B8": None,          # SBU 本设计不用
    })
# CC 各 5.1k 下拉:告诉 USB-C 供电端「我是设备,给我 5V」
add("R1", "Device", "R", 60, 50, "5.1k", R0402, {"1": "CC1", "2": "GND"})
add("R2", "Device", "R", 68, 50, "5.1k", R0402, {"1": "CC2", "2": "GND"})
# ESD:USBLC6 的 1/6、3/4 是同一条线的两端(穿过式),VBUS 脚做钳位参考
add("D1", "Power_Protection", "USBLC6-2SC6", 64, 80, "USBLC6-2SC6",
    "Package_TO_SOT_SMD:SOT-23-6", {
        "1": "USB_DP", "6": "USB_DP", "3": "USB_DN", "4": "USB_DN",
        "5": "VBUS", "2": "GND",
    })
flag("VBUS", 20, 30)
flag("GND", 28, 30)

# ── 3.3V LDO ───────────────────────────────────────────────────────────
# LP38693MP-3.3(TI SNVS321O):輸入絕對最大 12V、壓差 330mV @0.5A、額定 500mA。
# 原本用 AP2112K(絕對最大 6.5V),但 VBUS 只有 1µF 時熱插拔過衝模擬到 8.6V
# (sim/power_sim.py)。500mA 剛好滿足模組規格書「外部電源 ≥0.5A」。
add("U2", "Regulator_Linear", "LP38693MP-3.3", 100, 30, "LP38693MP-3.3",
    "Package_TO_SOT_SMD:SOT-223-5", {
        "4": "VSW", "1": "VSW",          # EN 接 IN:軟啟動後的電源一到就輸出(折返限流此時有效)
        "5": "GND", "3": "+3V3", "2": None,
    })
add("C1", "Device", "C", 82, 30, "1uF", C0402, {"1": "VBUS", "2": "GND"})
add("C2", "Device", "C", 118, 30, "10uF", C0805, {"1": "+3V3", "2": "GND"})
add("C3", "Device", "C", 126, 30, "100nF", C0402, {"1": "+3V3", "2": "GND"})

# ── VBUS 軟啟動(sim/softstart_sim.py)───────────────────────────────────
# 模組內部約 12.3µF + C2 10µF 掛在 LDO 後面,直接接 VBUS 插入時灌進約 79µC,
# 超過 USB 2.0 的 50µC(10µF 等效)。P-MOSFET 串在 VBUS 與 LDO 之間:
#   插入瞬間 C6 把閘極綁在源極 → 先關著;R9 慢慢把閘極拉向地 → 逐漸導通;
#   C7(閘-汲)讓輸出等斜率爬升:爬升段電流 80–97mA(Vth −0.5…−1.3V),3V3 1.3–3.7ms 就緒。
# AO3401A(AOS Rev 3.1):VDS −30V、VGS ±12V、RDS(on) <60mΩ @ −4.5V。
# 限制:拔掉後 C6 經 R9 放電(時間常數 10ms),拔插間隔太短時軟啟動不完整。
add("Q1", "Transistor_FET", "AO3401A", 100, 10, "AO3401A",
    "Package_TO_SOT_SMD:SOT-23", {"1": "SS_G", "2": "VBUS", "3": "VSW"})
add("R9", "Device", "R", 140, 10, "100k", R0402, {"1": "SS_G", "2": "GND"})
add("C6", "Device", "C", 148, 10, "100nF", C0402, {"1": "SS_G", "2": "VBUS"})
add("C7", "Device", "C", 156, 10, "10nF", C0402, {"1": "SS_G", "2": "VSW"})
add("C5", "Device", "C", 164, 10, "1uF", C0402, {"1": "VSW", "2": "GND"})
# VSW 只經 MOSFET(passive)進來,ERC 會判 LDO 的 power_in 未被驅動;這裡確實是電源入口
flag("VSW", 172, 10)

# ── ESP32-C3 模块 ──────────────────────────────────────────────────────
add("U1", "RF_Module", "ESP32-C3-WROOM-02", 170, 80, "ESP32-C3-WROOM-02-N4",
    "RF_Module:ESP32-C3-WROOM-02", {
        "1": "+3V3", "9": "GND", "19": "GND",
        "2": "EN",
        "8": "IO9",                      # BOOT
        "7": "IO8", "16": "IO2",         # strapping,上拉
        "13": "USB_DN", "14": "USB_DP",  # GPIO18 = D-,GPIO19 = D+
        "11": "RXD", "12": "TXD",
        "10": "LED_USER",
        "3": "IO4", "4": "IO5", "5": "IO6", "6": "IO7",
        "18": None, "17": None, "15": None,   # IO0 / IO1 / IO3 未引出
    })

# ── 复位与启动 ──────────────────────────────────────────────────────────
add("R3", "Device", "R", 110, 70, "10k", R0402, {"1": "+3V3", "2": "EN"})
add("C4", "Device", "C", 118, 70, "1uF", C0402, {"1": "EN", "2": "GND"})
add("SW1", "Switch", "SW_Push", 112, 88, "RESET", BUTTON, {"1": "EN", "2": "GND"})
add("R4", "Device", "R", 110, 110, "10k", R0402, {"1": "+3V3", "2": "IO9"})
add("SW2", "Switch", "SW_Push", 112, 128, "BOOT", BUTTON, {"1": "IO9", "2": "GND"})
add("R5", "Device", "R", 226, 50, "10k", R0402, {"1": "+3V3", "2": "IO8"})
add("R6", "Device", "R", 234, 50, "10k", R0402, {"1": "+3V3", "2": "IO2"})

# ── LED ────────────────────────────────────────────────────────────────
# Device:LED 是 1 = K(阴极)、2 = A(阳极)—— usbc-ldo 那块第一版就接反过,这里写死脚名
# LED 電流由 lib/review.py 檢查:藍光 Vf 2.5–3.6V,接 3.3V GPIO 幾乎不亮 → 改黃光;
# 綠光 Vf 2.6–3.1V,經 1k 只有約 0.45mA → 電阻改 220Ω(約 2mA)。
add("R7", "Device", "R", 226, 110, "470", R0402, {"1": "LED_USER", "2": "LED_USER_A"})
add("D2", "Device", "LED", 226, 128, "KT-0805Y", LED0805, {"2": "LED_USER_A", "1": "GND"})
add("R8", "Device", "R", 82, 110, "220", R0402, {"1": "+3V3", "2": "LED_PWR_A"})
add("D3", "Device", "LED", 82, 128, "GREEN", LED0805, {"2": "LED_PWR_A", "1": "GND"})

# ── 排针 ───────────────────────────────────────────────────────────────
add("J2", "Connector_Generic", "Conn_01x08", 250, 90, "IO",
    "Connector_PinHeader_2.54mm:PinHeader_1x08_P2.54mm_Vertical", {
        "1": "+3V3", "2": "GND", "3": "TXD", "4": "RXD",
        "5": "IO4", "6": "IO5", "7": "IO6", "8": "IO7",
    })

# ── 写出前自检 ─────────────────────────────────────────────────────────
bad = s.crossing_pins() + s.overlapping_wires()
if bad:
    print(f"!! 自检失败 {len(bad)} 项,拒绝写出:")
    for b in bad:
        print("   ", b)
    raise SystemExit(1)

(HERE.parent / "expected_nets.json").write_text(
    json.dumps(EXPECTED, indent=1, ensure_ascii=False, sort_keys=True), encoding="utf-8")
out = HERE.parent / "esp32c3.kicad_sch"
out.write_text(s.render(), encoding="utf-8", newline="\n")
print(f"wrote {out.name}: {len(s.parts)} parts, {len(s.labels)} labels")

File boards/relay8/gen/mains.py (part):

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SLOT_X = (2.3, 3.3)     # 槽相对 COM 的 x 范围(两侧对称),宽 1mm
SLOT_Y = (-6.0, 4.2)    # 槽相对 COM 的 y 范围:上端超过线圈焊盘,下端超过 COM 焊盘

LABELS = {"N_BUS": "N", "L_IN": "L"}    # 其余网取最后一段:RL3_NO → "NO"


def mm(v: float) -> int:
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        xs.append(com[0])
        segs.append((com, (com[0], l_y), "L_BUS", RISER_W, B))                    # COM → L_BUS
        npin = pad_xy(term, "2")
        segs.append((npin, (npin[0], n_y), "N_BUS", RISER_W, B))                  # 端子 N → N_BUS
        for relay_pin, term_pin in (("3", "1"), ("4", "3")):                      # NO、NC
            net = _net_of(relay, relay_pin)
            assert net == _net_of(term, term_pin), (relay.GetReference(), relay_pin)
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        b = (pcbnew.ToMM(c1.GetPosition().x), pcbnew.ToMM(c1.GetPosition().y))
        segs.append((a, b, c0.GetNetname(), INPUT_W, B))
    # RV1 的两个脚放在两条汇流排上,焊盘本身压在汇流排铜上即连通,不另拉线
    for pin, net in (("1", "L_BUS"), ("2", "N_BUS")):
        assert _net_of(rv1, pin) == net, ("RV1", pin)

    for a, b, net, width, layer in segs:
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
